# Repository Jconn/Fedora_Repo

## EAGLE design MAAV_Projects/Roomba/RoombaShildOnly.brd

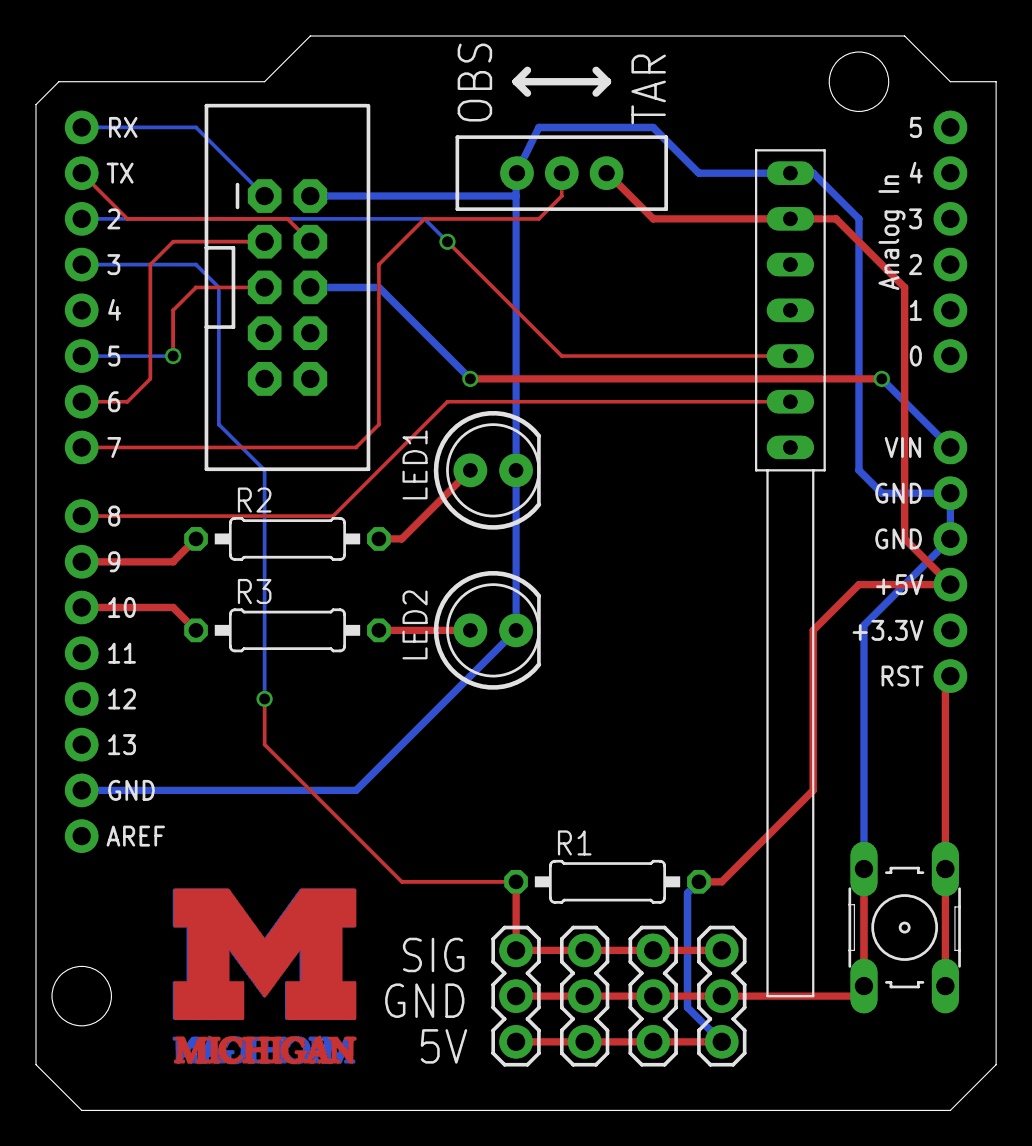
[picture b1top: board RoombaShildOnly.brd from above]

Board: 2 copper layers, 53.3 x 59.7 mm, 16 parts (1 on the bottom side), 16 nets.

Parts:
JP1: IROBOT_CREATE_IARC_HOOKUP; 2X5-SHROUDED
LED1: Green; LED5MM
LED2: Red; LED5MM
R1: 4.7k; 0207/10
R2, R3: 220; 0207/10
S1: SWITCH-SPDTTHRU-VERT; SWITCH-SPDT_THRU-VERT
S2: TACT_BUTTON_THRU-HOLE; SIMPLE_BUTTON
SV1: RF_RECIEVER_VERT
U2: ARDUINO_SHIELDLABEL; DUEMILANOVE_SHIELD
U$1, U$2, U$3, U$4: HALL_EFFECTHEADER; 1X03
U$12, U$13: BLOCK-M-STACKED_10MM_MASK

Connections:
5V: R1.2, S1.1, SV1.+5V, U2.5V, U$1.1, U$2.1, U$3.1, U$4.1
CREATE_BC: JP1.3, U2.D6
CREATE_PWR_TOG: JP1.5, U2.D5
CREATE_RX: JP1.4, U2.TX
CREATE_TX: JP1.1, U2.RX
GND: JP1.2, LED1.K, LED2.K, S1.3, S2.1, S2.2, SV1.GND, U2.GND@0, U2.GND@1, U2.GND@2, U$1.2, U$2.2, U$3.2, U$4.2
HALL_BUS: R1.1, U2.D3, U$1.3, U$2.3, U$3.3, U$4.3
LED_GREEN: R2.1, U2.D9
LED_RED: R3.1, U2.D10
unnamed: LED1.A, R2.2
unnamed: LED2.A, R3.2
RESET: S2.3, S2.4, U2.RES
RF_D2: SV1.D2, U2.D2
RF_D3: SV1.D3, U2.D8
SWITCH_1: S1.2, U2.D7
VIN: JP1.6, U2.VIN
